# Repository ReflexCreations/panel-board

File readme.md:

# RE:Flex Dance Panel v2 PCB Design 

This repository contains source documents and manufacturing files for the RE:Flex Dance Pad's Panel Board. It was created using [KiCAD 5.1.4](https://kicad.org/).

The Panel Boards purpose is to implement three subsystems underneath a standard dance pad 'panel':
- An interface for four [GML670 50kg Load Cell Sensors](http://www.gavincc.com/galoce/category-1/140.html). This subsystem conditions and amplifies the sensor differential input signals to prevent noise interference. The system is then sampled by an ADC at approximately 64kHz, and averaged to produce a clear 1kHz signal.
- Interface for a diamond-shaped grid of 84 RGB WS2813 LEDs at over 60Hz. On-board implementation of a 24->5V switch-mode power supply allows interface of standard brick PSUs to power a given board. There is also a 5V logic system for generating timing data that allows control of the RGB LED data.
- Interface for UART over RJ45, to communicate data from the I/O board for LED animations and to communicate data back to the I/O board for sensor data. The I/O USB interface allows for the generation of lighting data by computer program, and subsequent use of the analog sensor data gathered by Panel boards.

2. Place the order with [JLCPCB](https://jlcpcb.com)
```
    Open https://jlcpcb.com/ in your web browser.
    Click "Order Now" in the upper-right of the screen.
    Click "Add your gerber file", select the release-v2-RC2.zip file from the releases.
    Pick a PCB Qty.  It has to be a multiple of 5.  You will need 4 panel boards per platform.  Note that the per-board cost may reduce quite dramatically as you increase your order size.
    Pick a board color or leave it at the default green. Last time I checked different colors only affect build time, not price.
    Pick a surface finish or leave it on the default. The default is cheapest, but contains lead. ENIG gives the pads a nice golden finish instead of silver.
    Leave all the other options as they are.
    Scroll down to "SMT Assembly" and switch it on.  This means they will solder components on the board for you.  But not necessarily all of them.
    Select "assemble top side"
    Pick a quantity (SMT QTY).  If you picked 5 for the PCB Qty, you can choose to have only 2 assembled, to save money on parts and assembly fees.  Otherwise all of them will be assembled.
    Click "Confirm".
    On the right side of the page, click "Next"
    Click "Add BOM File"; upload the *release/bom.csv* file
    Click "Add CPL File"; upload the the *release/panel-board-top-pos.csv* file
    Click "Next"
    Review the specified parts; they should all be "confirmed" in the right column, so you can leave everything as it is.
        It's IMPORTANT to check this page carefully, as stock shortages are not at all uncommon, and will be reported on this page.
        If you proceed without addressing such issues, your order will go ahead but the missing components will be left out of the assembly process.  You will not be charged for these components, but they will not be mounted on your board either.
        Also note that this page only considers a single board when giving the cost for each component.  Don't worry.  The actual per-component cost you are charged will be based on the total quantity of the component mounted on all boards combined.  You will be able to confirm this in the Bill of Materials, viewable from the shopping cart page.
    Click "Next"
        In the preview, some ICs might look like they're oriented wrong. This is a problem with their viewer; the files are correct. If it ends up wrong (not aligning with the pads), they'll either correct it or email you to find a solution.
    Click "Save to cart"
        On the shopping cart page, you can access the Bill of Material for the SMT assembly, which will show exactly what you pay for each component.
        If the total cost here is lower than you expected, take it as a sign to double-check the Bill of Material and the "Unselected Parts" in the next tab, and look for parts that should have been supplied by JLCPCB but weren't.
    Click "Check out Securely"
    Add your shipping and billing details
    Select a shipping method. Usually the DHL-based ones are fine. You can gamble on whether or not you want duty and customs paid up front (more expensive), or hope for the best with the cheaper option, in which case you might get a bill from the courier later.
    Click "Continue" when you're happy
    Click "submit order"
    Do what you need to do for payment
    Wait for your boards to get delivered
```

3. Order the remaining through-hole parts - A list of these parts can be seen at `release/unpopulated.csv`. Companies that sell parts like this include Mouser, Digikey, RS-Components and Farnell.

4. Solder the remaining parts onto the board.  For some parts, you may need to work out a way to keep them from falling out from the board when you flip it upside-down to do the soldering.  I've heard of techniques including heat-resistant tape, folded paper towels and blu-tack.  You'll work something out, but keep in mind each method has its caveats, and don't forget you're dealing with a hot soldering iron, so take care.
    Here is a guide for each through-hole part on the panel board:
    J1 / Würth Elektronik 694106301002 / 2.1mm DC barrel jack connector: Easy.  Big contacts can take a lot of solder.
    J2 / Amphenol FCI 54602-908LF / Rj45/ethernet connector: Snaps onto the board with plastic tabs so you don't have to worry about holding it in place.  These large components can get in the way when soldering other components, so consider doing them last.
    J3 / 3M 30310-6002HB / 10-pin ST-LINK connector with plastic fence: By convention, the gap in the fence goes on the side with pin 1 - the pin with the square solder pad.  The gap also faces towards the edge of the board in this instance.
    J4 / Harwin M20-9980446 / External Logic connector: It's quite possible you'll never use this connector, so you could consider postponing this one until you actually need it, which might also reduce the chance of damage to the 74HCT245 level-shifter chip from ESD.  This one falls right out if not held in place, so you'll want to apply some technique as touched on above.
    J5,J6,J7,J8 / Japan Solderless Terminals B4B-PH-K-S(LF)(SN) / load cell sensor connectors: The gap in the fence goes towards the inside of the board.  If you're looking at the side of the connector with that gap, pin 1 is on the right.  Unless you're holding it upside-down.  Just point the gap towards the middle of the board and you'll be okay.  Though they have a little grip, I'd recommend you take steps (see above) to keep them in place when soldering.
    SW1,SW2 / TE Connectivity 1825910-6: The pins lock into the board so you don't have to worry about it falling out of position.  When these switches are placed correctly, the pins come out on the left and right sides.  It's possible to bend the pins the wrong way if you're careless during insertion, but it's easy to rectify.

## Future Improvements
- Under test, several boards had broken level shifters / microcontrollers due to ESD under improper handling. This shouldn't be a problem if taking proper ESD precaution. Reducing susceptibility to ESD would be important to improve reliability of these boards for end users, though.
- The LEDs don't need to be powered by 5V. Running 4V is perfectly reasonable. And running the microcontroller at 3.6V could remove the requirement for the level shifter IC. This'd save money and complexity.
- Currently, there's a lot of connectors. We could daisy chain a number of boards if we utilized the correct UART transmission protocol. My hope is eventually to just have 3 RJ45 connectors, which can each address a maximum of 3 panels. 
- Switching to lower power LEDs would be nice. Currently they're far too bright and reducing their power consumption could make some things easier.
- We could also eliminate the need for all of the output DC power jacks by running power along the RJ45 cable, similar to 'Power over Ethernet'. This would probably depend on using low power LEDs.
- Step-down converter update. Currently it's a bit unwieldy. With lower power LEDs we could switch the electrolytics for an array of multiceramics to improve reliability. This would also be necessary for the daisy chaining method.
- The RS-485 transceivers probably don't need direction-switching, and the transceiver is entirely deprecated connected to the USART clock lines. We could save some microcontroller pins by removing this. This'd also make firmware updates to panel boards over UART a lot easier.
- Setting a panel 'address' via DIP switches. This'd make it easier to transfer information back about the sensor data, and allow the panel to be identified by software as a 'Left' or 'Up-Right' or any other type of panel. Especially useful for future daisy chained 9 panel implementations.
- Easier debugging. The status LEDs are ambiguous as to what they do. More status LEDs, more text indication on the board (e.g. 'Active UART comms' next to a status LED) could make things a lot easier for the end user.
- Future form factor updates. People might want to use these boards in an arcade pad. They may want to avoid the aluminium extrusion framework. Fitting this board for all sorts of different requirements will improve accessibility to the electronics.
- Board that doesn't need LEDs, or use external LED power source for running the panels. This will make things significantly cheaper for other variants. This board could also avoid the expensive conditioning of load cells if it could interface FSRs and digital sensors. 
- These boards could have through hole parts populated by a batch manufacturer, and be sold without the need for soldering. If you'd like to sell these boards, please get in touch, and we can help you source finished boards.

## Firmware

For the board to function, you will need to install the panel board firmware to it. You can find this information within the repo for the Panel-Firmware.

## License

For license details, see LICENSE file

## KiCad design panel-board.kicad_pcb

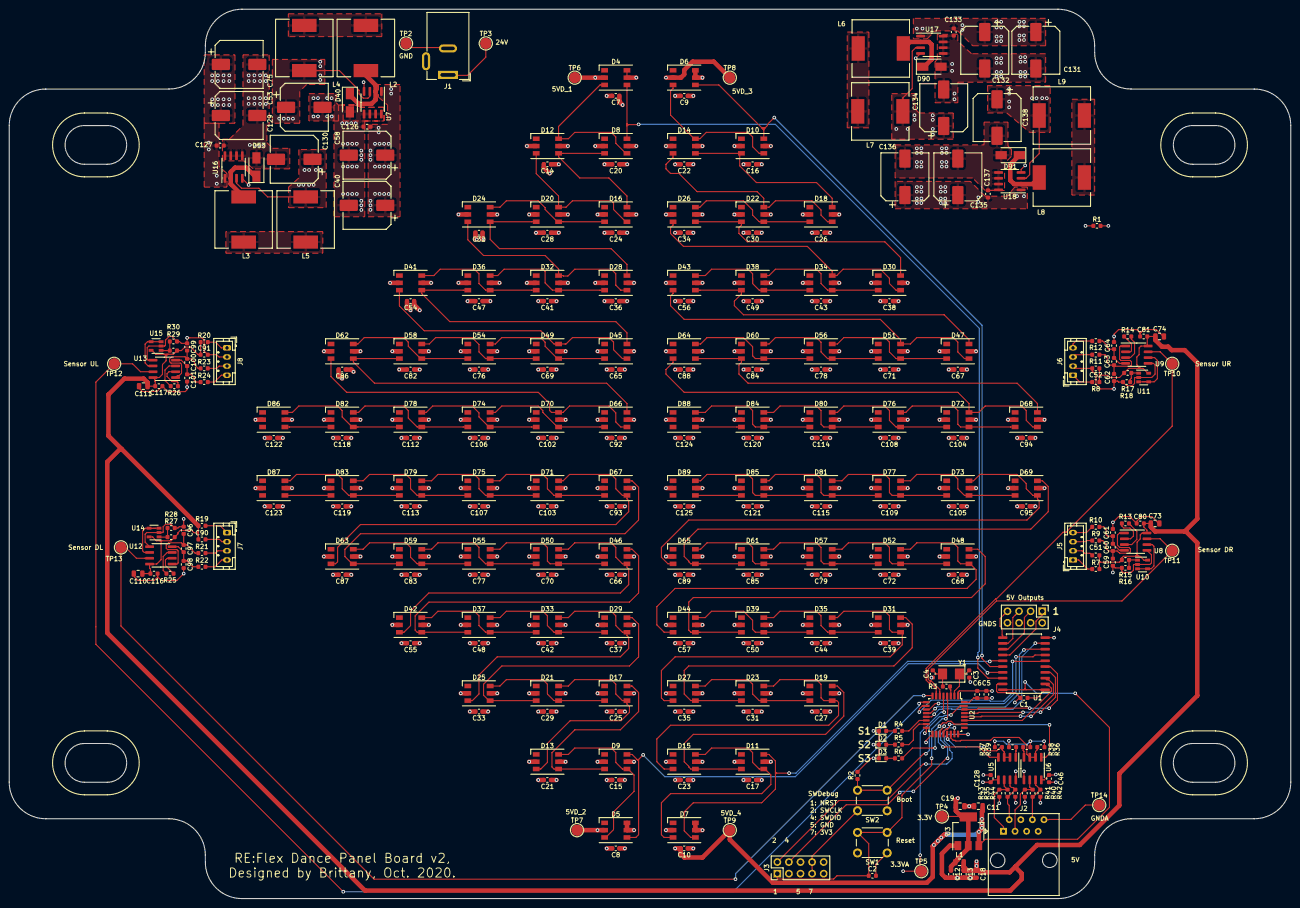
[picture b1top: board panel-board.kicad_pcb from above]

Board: 4 copper layers, 281.0 x 195.0 mm, 318 parts (0 on the bottom side), 176 nets.

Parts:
C1, C2, C5, C6, C7, C8, C9, C10, C14, C15, C16, C17, C18, C20, C21, C22, C23, C24, C25, C26, C27, C28, C29, C30, C31, C32, C33, C34, C35, C36, C37, C38, C39, C41, C42, C43, C44, C46, C47, C48, C49, C50, C51, C52, C54, C55, C56, C57, C65, C66, C67, C68, C69, C70, C71, C72, C76, C77, C78, C79, C80, C81, C82, C83, C84, C85, C86, C87, C88, C89, C90, C91, C92, C93, C94, C95, C102, C103, C104, C105, C106, C107, C108, C109, C112, C113, C114, C115, C116, C117, C118, C119, C120, C121, C122, C123, C124, C125, C126, C127, C128, C133, C137: 0.1u; C_0603_1608Metric
C3, C4: 22p; C_0603_1608Metric
C11, C73, C74, C110, C111: 10u; C_0805_2012Metric
C12, C13: 1u; C_0603_1608Metric
C19: 22u; C_0805_2012Metric
C40, C53, C58, C75, C129, C130, C131, C132, C134, C135, C136, C138: 220u; CP_Elec_10x10
C59, C61, C62, C64, C96, C98, C99, C101: 4.7n; C_0603_1608Metric
C60, C63, C97, C100: 470n; C_0603_1608Metric
D1, D2, D3: LED_Small; LED_0603_1608Metric
D4, D5, D6, D7, D8, D9, D10, D11, D12, D13, D14, D15, D16, D17, D18, D19, D20, D21, D22, D23, D24, D25, D26, D27, D28, D29, D30, D31, D32, D33, D34, D35, D36, D37, D38, D39, D41, D42, D43, D44, D45, D46, D47, D48, D49, D50, D51, D52, D54, D55, D56, D57, D58, D59, D60, D61, D62, D63, D64, D65, D66, D67, D68, D69, D70, D71, D72, D73, D74, D75, D76, D77, D78, D79, D80, D81, D82, D83, D84, D85, D86, D87, D88, D89: WS2813; LED_WS2812_PLCC6_5.0x5.0mm_P1.6mm
D40, D53, D90, D91: D_Schottky; D_SMA
J1: Barrel_Jack_MountingPin; BarrelJack_Wuerth_6941xx301002
J2: RJ45; RJ45_Amphenol_54602-x08_Horizontal
J3: Conn_02x05_Odd_Even; PinHeader_2x05_P2.54mm_Vertical
J4: Conn_02x04_Odd_Even; PinHeader_2x04_P2.54mm_Vertical
J5, J6, J7, J8: Conn_01x04_Male; JST_PH_B4B-PH-K_1x04_P2.00mm_Vertical
L1: SDFL2012Q1R0KTF; L_0805_2012Metric
L2, L3, L4, L5, L6, L7, L8, L9: 47u; L_12x12mm_H8mm
R1: 0R; R_0603_1608Metric
R2, R16, R18, R28, R30, R36, R37, R38, R39: 10k; R_0603_1608Metric
R3: 220R; R_0603_1608Metric
R4, R5, R6: 270R; R_0603_1608Metric
R7, R8, R19, R20: 470R; R_0603_1608Metric
R9, R10, R11, R12, R21, R22, R23, R24: 330R; R_0603_1608Metric
R13, R14, R25, R26, R35, R40: 100R; R_0603_1608Metric
R15, R17, R27, R29: 33k; R_0603_1608Metric
R41, R42, R43, R44: 360R; R_0603_1608Metric
SW1, SW2: SW_Push; SW_PUSH_6mm
TP2, TP3, TP4, TP5, TP6, TP7, TP8, TP9, TP10, TP11, TP12, TP13, TP14: TestPoint; TestPoint_Pad_D2.5mm
U1: 74HCT245; SOIC-20W_7.5x12.8mm_P1.27mm
U2: STM32F334K8Tx; LQFP-32_7x7mm_P0.8mm
U3: AMS1117-3.3; SOT-223-3_TabPin2
U5, U6: SP3485EN; SOIC-8_3.9x4.9mm_P1.27mm
U7, U16, U17, U18: XL1509-5.0E1; SOIC-8_3.9x4.9mm_P1.27mm
U8, U9, U12, U13: INA826; SOIC-8_3.9x4.9mm_P1.27mm
U10, U11, U14, U15: LMV321; SOT-23-5
Y1: 8MHz; Crystal_SMD_5032-2Pin_5.0x3.2mm

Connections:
5VD_1: C7.2, C14.2, C20.2, C24.2, C28.2, C32.2, C36.2, C41.2, C47.2, C54.2, C65.2, C69.2, C76.2, C82.2, C86.2, C92.2, C102.2, C106.2, C112.2, C118.2, C122.2, C129.1, D4.2 (VDD), D8.2 (VDD), D12.2 (VDD), D16.2 (VDD), D20.2 (VDD), D24.2 (VDD), D28.2 (VDD), D32.2 (VDD), D36.2 (VDD), D41.2 (VDD), D45.2 (VDD), D49.2 (VDD), D54.2 (VDD), D58.2 (VDD), D62.2 (VDD), D66.2 (VDD), D70.2 (VDD), D74.2 (VDD), D78.2 (VDD), D82.2 (VDD), D86.2 (VDD), L4.1, TP6.1, U7.3 (FB)
5VD_2: C8.2, C15.2, C21.2, C25.2, C29.2, C33.2, C37.2, C42.2, C48.2, C55.2, C66.2, C70.2, C77.2, C83.2, C87.2, C93.2, C103.2, C107.2, C113.2, C119.2, C123.2, C130.1, D5.2 (VDD), D9.2 (VDD), D13.2 (VDD), D17.2 (VDD), D21.2 (VDD), D25.2 (VDD), D29.2 (VDD), D33.2 (VDD), D37.2 (VDD), D42.2 (VDD), D46.2 (VDD), D50.2 (VDD), D55.2 (VDD), D59.2 (VDD), D63.2 (VDD), D67.2 (VDD), D71.2 (VDD), D75.2 (VDD), D79.2 (VDD), D83.2 (VDD), D87.2 (VDD), L5.1, TP7.1, U16.3 (FB)
5VD_3: C9.2, C16.2, C22.2, C26.2, C30.2, C34.2, C38.2, C43.2, C49.2, C56.2, C67.2, C71.2, C78.2, C84.2, C88.2, C94.2, C104.2, C108.2, C114.2, C120.2, C124.2, C134.1, D6.2 (VDD), D10.2 (VDD), D14.2 (VDD), D18.2 (VDD), D22.2 (VDD), D26.2 (VDD), D30.2 (VDD), D34.2 (VDD), D38.2 (VDD), D43.2 (VDD), D47.2 (VDD), D51.2 (VDD), D56.2 (VDD), D60.2 (VDD), D64.2 (VDD), D68.2 (VDD), D72.2 (VDD), D76.2 (VDD), D80.2 (VDD), D84.2 (VDD), D88.2 (VDD), L7.1, TP8.1, U17.3 (FB)
5VD_4: C1.1, C10.2, C11.1, C17.2, C23.2, C27.2, C31.2, C35.2, C39.2, C44.2, C50.2, C57.2, C68.2, C72.2, C79.2, C85.2, C89.2, C95.2, C105.2, C109.2, C115.2, C121.2, C125.2, C138.1, D7.2 (VDD), D11.2 (VDD), D15.2 (VDD), D19.2 (VDD), D23.2 (VDD), D27.2 (VDD), D31.2 (VDD), D35.2 (VDD), D39.2 (VDD), D44.2 (VDD), D48.2 (VDD), D52.2 (VDD), D57.2 (VDD), D61.2 (VDD), D65.2 (VDD), D69.2 (VDD), D73.2 (VDD), D77.2 (VDD), D81.2 (VDD), D85.2 (VDD), D89.2 (VDD), L9.1, TP9.1, U1.1 (A->B), U1.20 (VCC), U3.3 (VI), U18.3 (FB)
+3.3V: C5.2, C6.2, C12.1, C19.1, C46.2, C128.2, J3.7, J3.8, L1.1, R39.2, R41.2, R43.2, SW2.1, TP4.1, U2.1 (VDD), U2.17 (VDD), U3.2 (VO), U5.8 (VCC), U6.8 (VCC)
+3.3VA: C13.1, C18.1, C51.1, C52.1, C73.1, C74.1, C80.1, C81.1, C90.1, C91.1, C110.1, C111.1, C116.1, C117.1, L1.2, R7.2, R8.2, R15.2, R17.2, R19.2, R20.2, R27.2, R29.2, TP5.1, U2.5 (VDDA), U8.8 (Vs+), U9.8 (Vs+), U10.5 (V+), U11.5 (V+), U12.8 (Vs+), U13.8 (Vs+), U14.5 (V+), U15.5 (V+)
+24V: C40.1, C53.1, C58.1, C75.1, C126.1, C127.1, C131.1, C132.1, C133.1, C135.1, C136.1, C137.1, J1.1, TP3.1, U7.1 (VIN), U16.1 (VIN), U17.1 (VIN), U18.1 (VIN)
EXTERN1: J4.1, U1.14 (B4)
EXTERN1_3.3: U1.6 (A4), U2.10 (PA4)
EXTERN2: J4.3, U1.13 (B5)
EXTERN2_3.3: U1.7 (A5), U2.11 (PA5)
EXTERN3: J4.5, U1.12 (B6)
EXTERN3_3.3: U1.8 (A6), U2.12 (PA6)
EXTERN4: J4.7, U1.11 (B7)
EXTERN4_3.3: U1.9 (A7), U2.13 (PA7)
GND: C7.1, C8.1, C9.1, C10.1, C14.1, C15.1, C16.1, C17.1, C20.1, C21.1, C22.1, C23.1, C24.1, C25.1, C26.1, C27.1, C28.1, C29.1, C30.1, C31.1, C32.1, C33.1, C34.1, C35.1, C36.1, C37.1, C38.1, C39.1, C40.2, C41.1, C42.1, C43.1, C44.1, C47.1, C48.1, C49.1, C50.1, C53.2, C54.1, C55.1, C56.1, C57.1, C58.2, C65.1, C66.1, C67.1, C68.1, C69.1, C70.1, C71.1, C72.1, C75.2, C76.1, C77.1, C78.1, C79.1, C82.1, C83.1, C84.1, C85.1, C86.1, C87.1, C88.1, C89.1, C92.1, C93.1, C94.1, C95.1, C102.1, C103.1, C104.1, C105.1, C106.1, C107.1, C108.1, C109.1, C112.1, C113.1, C114.1, C115.1, C118.1, C119.1, C120.1, C121.1, C122.1, C123.1, C124.1, C125.1, C126.2, C127.2, C129.2, C130.2, C131.2, C132.2, C133.2, C134.2, C135.2, C136.2, C137.2, C138.2, D4.5 (GND), D4.6 (BIN), D5.5 (GND), D5.6 (BIN), D6.5 (GND), D6.6 (BIN), D7.5 (GND), D7.6 (BIN), D8.5 (GND), D9.5 (GND), D10.5 (GND), D11.5 (GND), D12.5 (GND), D13.5 (GND), D14.5 (GND), D15.5 (GND), D16.5 (GND), D17.5 (GND), D18.5 (GND), D19.5 (GND), D20.5 (GND), D21.5 (GND), D22.5 (GND), D23.5 (GND), D24.5 (GND), D25.5 (GND), D26.5 (GND), D27.5 (GND), D28.5 (GND), D29.5 (GND), D30.5 (GND), D31.5 (GND), D32.5 (GND), D33.5 (GND), D34.5 (GND), D35.5 (GND), D36.5 (GND), D37.5 (GND), D38.5 (GND), D39.5 (GND), D40.2 (A), D41.5 (GND), D42.5 (GND), D43.5 (GND), D44.5 (GND), D45.5 (GND), D46.5 (GND), D47.5 (GND), D48.5 (GND), D49.5 (GND), D50.5 (GND), D51.5 (GND), D52.5 (GND), D53.2 (A), D54.5 (GND), D55.5 (GND), D56.5 (GND), D57.5 (GND), D58.5 (GND), D59.5 (GND), D60.5 (GND), D61.5 (GND), D62.5 (GND), D63.5 (GND), D64.5 (GND), D65.5 (GND), D66.5 (GND), D67.5 (GND), D68.5 (GND), D69.5 (GND), D70.5 (GND), D71.5 (GND), D72.5 (GND), D73.5 (GND), D74.5 (GND), D75.5 (GND), D76.5 (GND), D77.5 (GND), D78.5 (GND), D79.5 (GND), D80.5 (GND), D81.5 (GND), D82.5 (GND), D83.5 (GND), D84.5 (GND), D85.5 (GND), D86.5 (GND), D87.5 (GND), D88.5 (GND), D89.5 (GND), D90.2 (A), D91.2 (A), J1.2, R1.1, TP2.1, U7.4 (~EN), U7.5 (GND), U7.6 (GND), U7.7 (GND), U7.8 (GND), U16.4 (~EN), U16.5 (GND), U16.6 (GND), U16.7 (GND), U16.8 (GND), U17.4 (~EN), U17.5 (GND), U17.6 (GND), U17.7 (GND), U17.8 (GND), U18.4 (~EN), U18.5 (GND), U18.6 (GND), U18.7 (GND), U18.8 (GND)
GNDA: C1.2, C2.1, C3.1, C4.1, C5.1, C6.1, C11.2, C12.2, C13.2, C18.2, C19.2, C46.1, C51.2, C52.2, C59.1, C61.2, C62.1, C64.2, C73.2, C74.2, C80.2, C81.2, C90.2, C91.2, C96.1, C98.2, C99.1, C101.2, C110.2, C111.2, C116.2, C117.2, C128.1, D1.1 (K), D2.1 (K), D3.1 (K), J2.8, J3.5, J3.6, J4.2, J4.4, J4.6, J4.8, J5.2, J6.2, J7.2, J8.2, R1.2, R2.2, R16.1, R18.1, R28.1, R30.1, R36.2, R37.2, R38.2, R42.2, R44.2, SW1.1, TP14.1, U1.10 (GND), U1.19 (CE), U2.16 (VSS), U2.32 (VSS), U3.1 (GND), U5.5 (GND), U6.5 (GND), U8.5 (Vs-), U9.5 (Vs-), U10.2 (V-), U11.2 (V-), U12.5 (Vs-), U13.5 (Vs-), U14.2 (V-), U15.2 (V-)
LEDA: D4.4 (DIN), D8.6 (BIN), U1.18 (B0)
LEDA_3.3: U1.2 (A0), U2.27 (PB4)
LEDB: D5.4 (DIN), D9.6 (BIN), U1.17 (B1)
LEDB_3.3: U1.3 (A1), U2.28 (PB5)
LEDC: D6.4 (DIN), D10.6 (BIN), U1.16 (B2)
LEDC_3.3: U1.4 (A2), U2.29 (PB6)
LEDD: D7.4 (DIN), D11.6 (BIN), U1.15 (B3)
LEDD_3.3: U1.5 (A3), U2.30 (PB7)
NRST: C2.2, J3.1, SW1.2, U2.4 (NRST)
unnamed: C3.2, U2.2 (PF0), Y1.1
unnamed: C4.2, R3.2, Y1.2
unnamed: C59.2, C60.1, R9.1, U8.1 (-)
unnamed: C60.2, C61.1, R10.1, U8.4 (+)
unnamed: C62.2, C63.1, R11.1, U9.1 (-)
unnamed: C63.2, C64.1, R12.1, U9.4 (+)
unnamed: C96.2, C97.1, R21.1, U12.1 (-)
unnamed: C97.2, C98.1, R22.1, U12.4 (+)
unnamed: C99.2, C100.1, R23.1, U13.1 (-)
unnamed: C100.2, C101.1, R24.1, U13.4 (+)
unnamed: D1.2 (A), R4.2
unnamed: D2.2 (A), R5.2
unnamed: D3.2 (A), R6.2
unnamed: D10.3 (DOUT), D14.4 (DIN), D18.6 (BIN)
unnamed: D6.3 (DOUT), D10.4 (DIN), D14.6 (BIN)
unnamed: D11.3 (DOUT), D15.4 (DIN), D19.6 (BIN)
unnamed: D7.3 (DOUT), D11.4 (DIN), D15.6 (BIN)
unnamed: D12.3 (DOUT), D16.4 (DIN), D20.6 (BIN)
unnamed: D8.3 (DOUT), D12.4 (DIN), D16.6 (BIN)
unnamed: D4.3 (DOUT), D8.4 (DIN), D12.6 (BIN)
unnamed: D13.3 (DOUT), D17.4 (DIN), D21.6 (BIN)
unnamed: D9.3 (DOUT), D13.4 (DIN), D17.6 (BIN)
unnamed: D5.3 (DOUT), D9.4 (DIN), D13.6 (BIN)
unnamed: D14.3 (DOUT), D18.4 (DIN), D22.6 (BIN)
unnamed: D15.3 (DOUT), D19.4 (DIN), D23.6 (BIN)
unnamed: D16.3 (DOUT), D20.4 (DIN), D24.6 (BIN)
unnamed: D17.3 (DOUT), D21.4 (DIN), D25.6 (BIN)
unnamed: D18.3 (DOUT), D22.4 (DIN), D26.6 (BIN)
unnamed: D19.3 (DOUT), D23.4 (DIN), D27.6 (BIN)
unnamed: D20.3 (DOUT), D24.4 (DIN), D28.6 (BIN)
unnamed: D21.3 (DOUT), D25.4 (DIN), D29.6 (BIN)
unnamed: D22.3 (DOUT), D26.4 (DIN), D30.6 (BIN)
unnamed: D23.3 (DOUT), D27.4 (DIN), D31.6 (BIN)
unnamed: D24.3 (DOUT), D28.4 (DIN), D32.6 (BIN)
unnamed: D25.3 (DOUT), D29.4 (DIN), D33.6 (BIN)
unnamed: D26.3 (DOUT), D30.4 (DIN), D34.6 (BIN)
unnamed: D27.3 (DOUT), D31.4 (DIN), D35.6 (BIN)
unnamed: D28.3 (DOUT), D32.4 (DIN), D36.6 (BIN)
unnamed: D29.3 (DOUT), D33.4 (DIN), D37.6 (BIN)
unnamed: D30.3 (DOUT), D34.4 (DIN), D38.6 (BIN)
unnamed: D31.3 (DOUT), D35.4 (DIN), D39.6 (BIN)
unnamed: D32.3 (DOUT), D36.4 (DIN), D41.6 (BIN)
unnamed: D33.3 (DOUT), D37.4 (DIN), D42.6 (BIN)
unnamed: D34.3 (DOUT), D38.4 (DIN), D43.6 (BIN)
unnamed: D35.3 (DOUT), D39.4 (DIN), D44.6 (BIN)
unnamed: D36.3 (DOUT), D41.4 (DIN), D45.6 (BIN)
unnamed: D37.3 (DOUT), D42.4 (DIN), D46.6 (BIN)
unnamed: D38.3 (DOUT), D43.4 (DIN), D47.6 (BIN)
unnamed: D39.3 (DOUT), D44.4 (DIN), D48.6 (BIN)
unnamed: D40.1 (K), L2.1, U7.2 (VOUT)
unnamed: D41.3 (DOUT), D45.4 (DIN), D49.6 (BIN)
unnamed: D42.3 (DOUT), D46.4 (DIN), D50.6 (BIN)
unnamed: D43.3 (DOUT), D47.4 (DIN), D51.6 (BIN)
unnamed: D44.3 (DOUT), D48.4 (DIN), D52.6 (BIN)
unnamed: D45.3 (DOUT), D49.4 (DIN), D54.6 (BIN)
unnamed: D46.3 (DOUT), D50.4 (DIN), D55.6 (BIN)
unnamed: D47.3 (DOUT), D51.4 (DIN), D56.6 (BIN)
unnamed: D48.3 (DOUT), D52.4 (DIN), D57.6 (BIN)
unnamed: D49.3 (DOUT), D54.4 (DIN), D58.6 (BIN)
unnamed: D50.3 (DOUT), D55.4 (DIN), D59.6 (BIN)
unnamed: D51.3 (DOUT), D56.4 (DIN), D60.6 (BIN)
unnamed: D52.3 (DOUT), D57.4 (DIN), D61.6 (BIN)
unnamed: D53.1 (K), L3.1, U16.2 (VOUT)
unnamed: D54.3 (DOUT), D58.4 (DIN), D62.6 (BIN)
unnamed: D55.3 (DOUT), D59.4 (DIN), D63.6 (BIN)
unnamed: D56.3 (DOUT), D60.4 (DIN), D64.6 (BIN)
unnamed: D57.3 (DOUT), D61.4 (DIN), D65.6 (BIN)
unnamed: D58.3 (DOUT), D62.4 (DIN), D66.6 (BIN)
unnamed: D59.3 (DOUT), D63.4 (DIN), D67.6 (BIN)
unnamed: D60.3 (DOUT), D64.4 (DIN), D68.6 (BIN)
unnamed: D61.3 (DOUT), D65.4 (DIN), D69.6 (BIN)
unnamed: D62.3 (DOUT), D66.4 (DIN), D70.6 (BIN)
unnamed: D63.3 (DOUT), D67.4 (DIN), D71.6 (BIN)
unnamed: D64.3 (DOUT), D68.4 (DIN), D72.6 (BIN)
unnamed: D65.3 (DOUT), D69.4 (DIN), D73.6 (BIN)
unnamed: D66.3 (DOUT), D70.4 (DIN), D74.6 (BIN)
unnamed: D67.3 (DOUT), D71.4 (DIN), D75.6 (BIN)
unnamed: D68.3 (DOUT), D72.4 (DIN), D76.6 (BIN)
unnamed: D69.3 (DOUT), D73.4 (DIN), D77.6 (BIN)
unnamed: D70.3 (DOUT), D74.4 (DIN), D78.6 (BIN)
unnamed: D71.3 (DOUT), D75.4 (DIN), D79.6 (BIN)
unnamed: D72.3 (DOUT), D76.4 (DIN), D80.6 (BIN)
unnamed: D73.3 (DOUT), D77.4 (DIN), D81.6 (BIN)
unnamed: D74.3 (DOUT), D78.4 (DIN), D82.6 (BIN)
unnamed: D75.3 (DOUT), D79.4 (DIN), D83.6 (BIN)
unnamed: D76.3 (DOUT), D80.4 (DIN), D84.6 (BIN)
unnamed: D77.3 (DOUT), D81.4 (DIN), D85.6 (BIN)
unnamed: D78.3 (DOUT), D82.4 (DIN), D86.6 (BIN)
unnamed: D79.3 (DOUT), D83.4 (DIN), D87.6 (BIN)
unnamed: D80.3 (DOUT), D84.4 (DIN), D88.6 (BIN)
unnamed: D81.3 (DOUT), D85.4 (DIN), D89.6 (BIN)
unnamed: D82.3 (DOUT), D86.4 (DIN)
unnamed: D83.3 (DOUT), D87.4 (DIN)
unnamed: D84.3 (DOUT), D88.4 (DIN)
unnamed: D85.3 (DOUT), D89.4 (DIN)
unnamed: D90.1 (K), L6.1, U17.2 (VOUT)
unnamed: D91.1 (K), L8.1, U18.2 (VOUT)
unnamed: J5.1, R7.1
unnamed: J5.3, R9.2
unnamed: J5.4, R10.2
unnamed: J6.1, R8.1
unnamed: J6.3, R11.2
unnamed: J6.4, R12.2
unnamed: J7.1, R19.1
unnamed: J7.3, R21.2
unnamed: J7.4, R22.2
unnamed: J8.1, R20.1
unnamed: J8.3, R23.2
unnamed: J8.4, R24.2
unnamed: L2.2, L4.2
unnamed: L3.2, L5.2
unnamed: L6.2, L7.2
unnamed: L8.2, L9.2
unnamed: R2.1, SW2.2, U2.31 (BOOT0)
unnamed: R3.1, U2.3 (PF1)
unnamed: R4.1, U2.14 (PB0)
unnamed: R5.1, U2.15 (PB1)
unnamed: R6.1, U2.26 (PB3)
unnamed: R13.1, U8.2 (Rg)
unnamed: R13.2, U8.3 (Rg)
unnamed: R14.1, U9.2 (Rg)
unnamed: R14.2, U9.3 (Rg)
unnamed: R15.1, R16.2, U10.1 (+)
unnamed: R17.1, R18.2, U11.1 (+)
unnamed: R25.1, U12.2 (Rg)
unnamed: R25.2, U12.3 (Rg)
unnamed: R26.1, U13.2 (Rg)
unnamed: R26.2, U13.3 (Rg)
unnamed: R27.1, R28.2, U14.1 (+)
unnamed: R29.1, R30.2, U15.1 (+)
unnamed: R38.1, U6.4 (DI)
unnamed: R39.1, U5.1 (RO)
unnamed: U8.6 (Ref), U10.3 (-), U10.4
unnamed: U9.6 (Ref), U11.3 (-), U11.4
unnamed: U12.6 (Ref), U14.3 (-), U14.4
unnamed: U13.6 (Ref), U15.3 (-), U15.4
RX+: J2.3, R40.2, R41.1, U6.6 (A)
RX-: J2.6, R40.1, R42.1, U6.7 (B)
RX_EN: R36.1, U2.22 (PA12), U6.2 (~RE), U6.3 (DE)
SENS1: TP11.1, U2.6 (PA0), U8.7
SENS2: TP10.1, U2.7 (PA1), U9.7
SENS3: TP13.1, U2.8 (PA2), U12.7
SENS4: TP12.1, U2.9 (PA3), U13.7
SWCLK: J3.2, U2.24 (PA14)
SWDIO: J3.4, U2.23 (PA13)
TX+: J2.1, R35.2, R43.1, U5.6 (A)
TX-: J2.2, R35.1, R44.1, U5.7 (B)
TX_EN: R37.1, U2.21 (PA11), U5.2 (~RE), U5.3 (DE)
UART_RX: U2.20 (PA10), U6.1 (RO)
UART_TX: U2.19 (PA9), U5.4 (DI)

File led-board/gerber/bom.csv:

Comment,Designator,Footprint,LCSC
470n,"C100,C97,C60,C63",Capacitor_SMD:C_0603_1608Metric,C1623
4.7n,"C101,C99,C98,C96,C59,C61,C62,C64",Capacitor_SMD:C_0603_1608Metric,C53987
10u,"C11,C111,C110,C73,C74",Capacitor_SMD:C_0805_2012Metric,C15850
1u,"C12,C13",Capacitor_SMD:C_0603_1608Metric,C15849
220u,"C131,C134,C132,C135,C138,C136,C53,C130,C75,C40,C129,C58",Capacitor_SMD:CP_Elec_10x10,C176670
22u,C19,Capacitor_SMD:C_0805_2012Metric,C45783
0.1u,"C2,C6,C5,C1,C18,C91,C117,C90,C116,C80,C51,C81,C52,C7,C14,C20,C24,C28,C32,C36,C41,C47,C54,C65,C69,C76,C82,C86,C92,C102,C106,C112,C118,C122,C8,C15,C21,C25,C29,C33,C37,C42,C48,C55,C66,C70,C77,C83,C87,C93,C103,C107,C113,C119,C123,C9,C16,C22,C26,C30,C34,C38,C43,C49,C56,C67,C71,C78,C84,C88,C94,C104,C108,C114,C120,C124,C10,C17,C23,C27,C31,C35,C39,C44,C50,C57,C68,C72,C79,C85,C89,C95,C105,C109,C115,C121,C125,C46,C45,C133,C137,C127,C126,C128",Capacitor_SMD:C_0603_1608Metric,C14663
22p,"C4,C3",Capacitor_SMD:C_0603_1608Metric,C1653
LED_Small,"D2,D3,D1",LED_SMD:LED_0603_1608Metric,C72043
WS2813,"D4,D8,D12,D16,D20,D24,D28,D32,D36,D41,D45,D49,D54,D58,D62,D66,D70,D74,D78,D82,D86,D5,D9,D13,D17,D21,D25,D29,D33,D37,D42,D46,D50,D55,D59,D63,D67,D71,D75,D79,D83,D87,D6,D10,D14,D18,D22,D26,D30,D34,D38,D43,D47,D51,D56,D60,D64,D68,D72,D76,D80,D84,D88,D7,D11,D15,D19,D23,D27,D31,D35,D39,D44,D48,D52,D57,D61,D65,D69,D73,D77,D81,D85,D89",LED_SMD:LED_WS2812_PLCC6_5.0x5.0mm_P1.6mm,C114592
D_Schottky,"D90,D91,D53,D40",Diode_SMD:D_SMA,C8678
Barrel_Jack_MountingPin,J1,Connector_BarrelJack:BarrelJack_CUI_PJ-102AH_Horizontal,NOT FITTED
RJ45,J2,Connector_RJ:RJ45_Amphenol_54602-x08_Horizontal,NOT FITTED
Conn_02x05_Odd_Even,J3,Connector_PinHeader_2.54mm:PinHeader_2x05_P2.54mm_Vertical,NOT FITTED
Conn_02x04_Odd_Even,J4,Connector_PinHeader_2.54mm:PinHeader_2x04_P2.54mm_Vertical,NOT FITTED
Conn_01x04_Male,"J7,J8,J5,J6",Connector_JST:JST_PH_B4B-PH-K_1x04_P2.00mm_Vertical,NOT FITTED
SDFL2012Q1R0KTF,L1,Inductor_SMD:L_0805_2012Metric,C1042
47u,"L7,L6,L9,L8,L5,L3,L4,L2",Inductor_SMD:L_12x12mm_H8mm,C169398
10k,"R2,R28,R18,R16,R30",Resistor_SMD:R_0603_1608Metric,C25804
330R,"R24,R23,R22,R21,R9,R10,R11,R12",Resistor_SMD:R_0603_1608Metric,C23138
100R,"R26,R25,R13,R14",Resistor_SMD:R_0603_1608Metric,C22775
33k,"R27,R17,R15,R29",Resistor_SMD:R_0603_1608Metric,C4216
220R,R3,Resistor_SMD:R_0603_1608Metric,C22962
360R,"R34,R36,R33,R31,R40,R38",Resistor_SMD:R_0603_1608Metric,C25194
120R,"R35,R32,R39",Resistor_SMD:R_0603_1608Metric,C22787
0R,"R41,R42,R37,R1",Resistor_SMD:R_0603_1608Metric,C21189
270R,"R5,R6,R4",Resistor_SMD:R_0603_1608Metric,C22966
470R,"R8,R7,R19,R20",Resistor_SMD:R_0603_1608Metric,C23179
SW_Push,"SW2,SW1",Button_Switch_THT:SW_PUSH-12mm,NOT FITTED
TestPoint,"TP10,TP11,TP13,TP12,TP5,TP4,TP3,TP2,TP8,TP9,TP7,TP6,TP1,TP14",TestPoint:TestPoint_Pad_D2.5mm,NOT FITTED
74HCT245,U1,Package_SO:SOIC-20W_7.5x12.8mm_P1.27mm,C5979
LMV321,"U10,U11,U14,U15",Package_TO_SOT_SMD:SOT-23-5,C7972
INA826,"U13,U12,U8,U9",Package_SO:SOIC-8_3.9x4.9mm_P1.27mm,C38433
XL1509-5.0E1,"U17,U18,U16,U7",Package_SO:SOIC-8_3.9x4.9mm_P1.27mm,C61063
STM32F334K8Tx,U2,Package_QFP:LQFP-32_7x7mm_P0.8mm,C106758
AMS1117-3.3,U3,Package_TO_SOT_SMD:SOT-223-3_TabPin2,C6186
SP3485EN,"U5,U4,U6",Package_SO:SOIC-8_3.9x4.9mm_P1.27mm,C8963
8MHz,Y1,Crystal:Crystal_SMD_5032-2Pin_5.0x3.2mm,C115962

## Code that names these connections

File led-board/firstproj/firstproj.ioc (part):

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Mcu.Name=STM32F334K(4-6-8)Tx
Mcu.Package=LQFP32
Mcu.UserName=STM32F334K8Tx
PA0.Mode=IN1-Single-Ended
PA0.Signal=ADC1_IN1
PA1.Mode=IN2-Single-Ended
PA1.Signal=ADC1_IN2
PA10.Mode=Synchronous
PA10.Signal=USART1_RX
PA11.Signal=GPIO_Output
PA12.Signal=GPIO_Output
PA13.Mode=Serial_Wire
PA13.Signal=SYS_JTMS-SWDIO
PA14.Mode=Serial_Wire
PA14.Signal=SYS_JTCK-SWCLK
PA15.Signal=GPIO_Output
PA2.Mode=IN3-Single-Ended
PA2.Signal=ADC1_IN3
PA3.Mode=IN4-Single-Ended
PA3.Signal=ADC1_IN4
PA4.Signal=GPIO_Output
PA5.Signal=GPIO_Output
PA6.Signal=GPIO_Output
PA7.Signal=GPIO_Output
PA8.Mode=Synchronous
PA8.Signal=USART1_CK
PA9.Mode=Synchronous
PA9.Signal=USART1_TX
PB0.Signal=GPIO_Output
PB1.Signal=GPIO_Output
PB3.Signal=GPIO_Output
PB4.Signal=GPIO_Output
PB5.Signal=GPIO_Output
PB6.Signal=GPIO_Output
PB7.Signal=GPIO_Output
PF0\ /\ OSC_IN.Mode=HSE-External-Oscillator
PF0\ /\ OSC_IN.Signal=RCC_OSC_IN
PF1\ /\ OSC_OUT.Mode=HSE-External-Oscillator
PF1\ /\ OSC_OUT.Signal=RCC_OSC_OUT
RCC.HSEPLLFreq_Value=8000000
RCC.HSE_VALUE=8000000
RCC.SYSCLKFreq_VALUE=72000000
RCC.SYSCLKSourceVirtual=RCC_SYSCLKSOURCE_PLLCLK
board=custom

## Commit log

2020-09-03 pre-layout
2020-09-06 Layout complete
2020-09-06 Output files
2020-09-07 Transceiver fix + output mask
2020-09-07 Sanity save
2020-09-07 Post v0.2 order commit
2020-09-08 Re-org.
2020-09-22 does this work?
2020-09-22 LEDs and ADC working, separately
2020-10-20 Staged for v2 release
2020-11-08 Supply power externally, and move sensor position
2020-11-08 Re-stage step file
2020-11-08 Positioning update
2020-12-12 Fix symbol library table, adding INA826 lib
    This fixes a missing symbol in the schematic.
2020-12-12 Update to reflect minimum required order quantity
2021-01-17 Improve the instructions in the readme.md file.
    Mainly trying to address problems and challenges found by the early builders.
2021-01-20 Change the presentation of questionable techniques to a style of "here's an idea, but I'm no expert and you're ultimately the one responsible for your soldering".
    Important because a reader could easily make the mistake of assuming a single author who is experienced in soldering.
2021-11-08 Update readme.md
    https://forum.kicad.info/t/warning-avoid-all-links-to-kicad-pcb-org-use-kicad-org/31521
2024-07-24 Schem for RS485 circuit corrections
2024-07-25 Finish PCB RS-485 fixes
2024-07-25 RS-485 updates: panel board
2024-07-26 RS-485 transceiver fixes - production
